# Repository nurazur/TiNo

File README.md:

# TiNo
[German Version](https://github.com/nurazur/TiNo/blob/master/LIESMICH.md)

"**TI**ny **NO**de": battery powered wireless sensor or wireless actor.
Target of the project is the development of small size , cost effective battery powered wireless sensors. The sensors communicate with gateways, like a raspberry pi.
The targets are:

- low cost (BOM under 5 Euro, as of 2020)
- very small size (matchbox)
- ultra low sleep current
- long battery life time: 5 years and more on a CR2032 cell
- long range (what ever this means :-), but its realy long)
- simple to build up
- communication security
- Plug&Play Firmware

Sensors can be almost any, like temperature, relative humidity, air pressure, altitude meter, light intensity, UV Index,
movement detectors, Reed switches, etc. However sensors have to be specified to work down to 2.2V. Otherwise the charge of the battery can not be fully used.

PCBs fit into low cost PVC boxes with the size of a matchbox that are readily available on the market.  

# Features
## General
- Voltage from ca. 1.8V to 3.6V
- Operates with a CR2032 cell up to 5 years
- various PCBs fitting into selected PVC boxes

## Sensors
- HTU21D
- SHT21, SHT20, SHT25
- SHT30, SHT31, SHT35
- BME280 (air pressure sensor)
- DS18B20 (ubiquitous temperature sensor)
- MAX31865 (PT100 temperature Sensor)
- AM312 (PIR movement sensor)
- I2C Bus based sensors can easily be integrated
- 4 digital GPIOs
- up to 4 analog GPIO's (dependent on hardware)

## Radio
- RFM69CW, RFM69HCW, RFM95 Module
- bidirectional communication
- ISM Band (Europe: 433MHz / 868MHz, US:315MHz / 915Mhz)
- 2GFSK Modulation
- Center frequency adjustable
- Frequency correction can be calibrated
- Transmit power from -18 dBm to 20dBm, 10 dBm typ.
- Link budget up to 120dB
- sensitivity -105 dBm typ.
- range t.b.d., but its looong!
- RF communication encrypted
- FEC (Forward Error Correction)
- Interleaver

## Baseband
- Atmel (Microchip) ATMega328p-au
- 32kByte Flash
- sleep current < 2µA mit external crystal 32.768kHz
- sleep current ca. 4µA with internal RC oscillator
- 1 MHz clock allows operating voltage down to 1.8V
- 8 MHz clock for gateway receiver
- I2C bus
- min 4 additional GPIO
- CPU can be locked to avoid reading the flash code

## System / Software
- Open Source Software C++
- Software can easily be adopted individually
- Programming tool is Arduino IDE
- Configuration of Nodes via serial interface (FTDI Adapter)
- configuration data and calibration data reside in EEPROM
- EEPROM encrypted
- Flashing
  - using ISP Adapter or
  - serial with FTDI Adapter and Bootloader
- up to 4 external interrupts (i.e. push buttons) can be configured

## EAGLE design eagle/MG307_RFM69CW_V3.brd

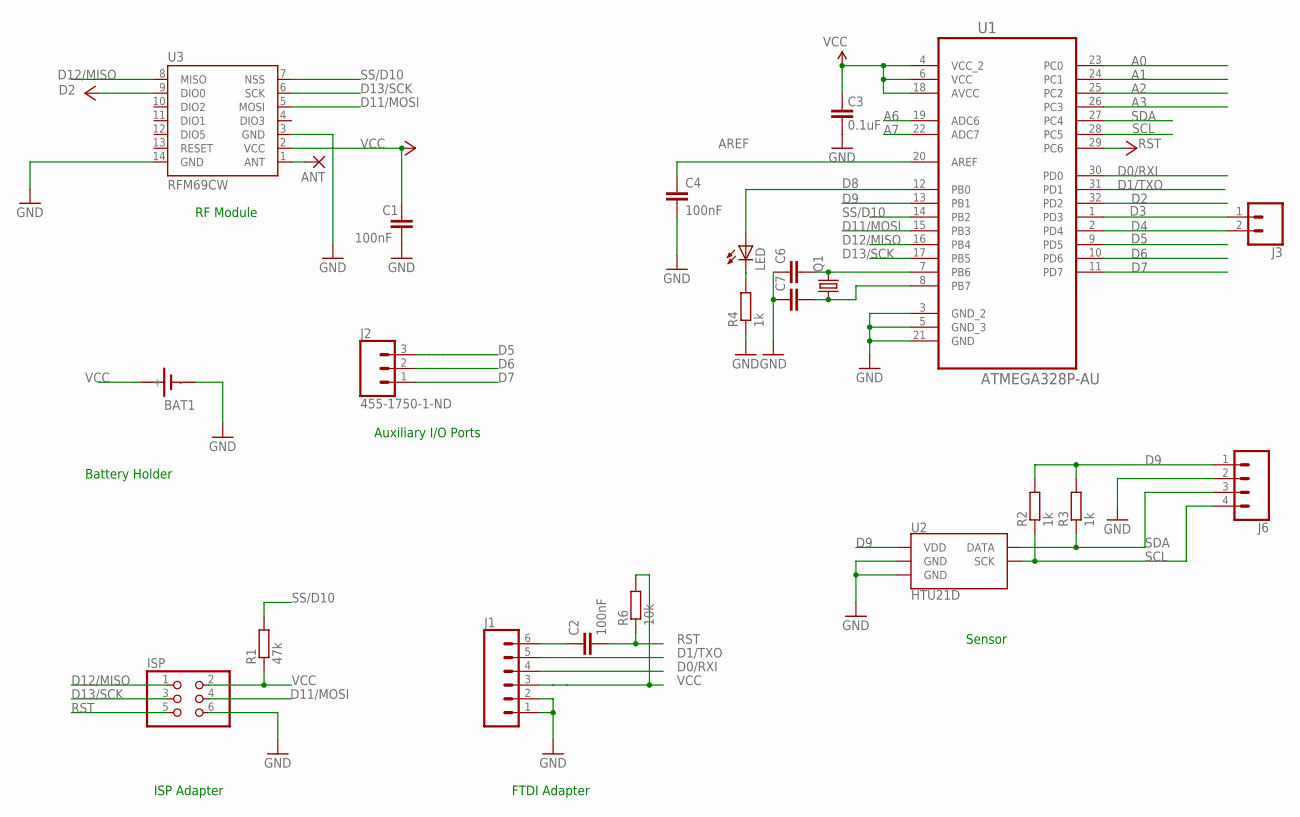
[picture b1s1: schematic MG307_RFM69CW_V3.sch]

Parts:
ANT: WIREPAD1,6/0,9; 1,6/0,9
BAT1: SN2032
C1, C2, C4: 100nF; C0603
C3: 0.1uF; 0603-CAP
C6, C7: C-EUC0402; C0402
ISP: PINHD-2X3; 2X03
J1: CONN_06SILK_FEMALE_PTH; 1X06
J2: 455-1750-1-ND; 1X03
J3: CONN_02; 1X02
J6: CONN_04; 1X04
LED: LEDCHIPLED_0603; CHIPLED_0603
Q1: CRYSTALTC26V; TC26V
R1: 47k; R0603
R2, R3, R4: 1k; R0603
R6: 10k; R0603
U1: ATMEGA328P-AU; QFP80P900X900X120-32N
U2: HTU21D; DFN-6-3X3-HTU21D
U3: RFM69CW

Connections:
A0: U1.23 (PC0)
A1: U1.24 (PC1)
A2: U1.25 (PC2)
A3: U1.26 (PC3)
A6: U1.19 (ADC6)
A7: U1.22 (ADC7)
ANT: ANT.1, U3.1 (ANT)
AREF: C4.1, U1.20 (AREF)
D0/RXI: J1.4, U1.30 (PD0)
D1/TXO: J1.5, U1.31 (PD1)
D2: U1.32 (PD2), U3.9 (DIO0)
D3: J3.1, U1.1 (PD3)
D4: J3.2, U1.2 (PD4)
D5: J2.3, U1.9 (PD5)
D6: J2.2, U1.10 (PD6)
D7: J2.1, U1.11 (PD7)
D8: LED.A, U1.12 (PB0)
D9: J6.1, R2.2, R3.2, U1.13 (PB1), U2.VDD
D11/MOSI: ISP.4, U1.15 (PB3), U3.5 (MOSI)
D12/MISO: ISP.1, U1.16 (PB4), U3.8 (MISO)
D13/SCK: ISP.3, U1.17 (PB5), U3.6 (SCK)
DTR: C2.1, J1.6
GND: BAT1.-, C1.2, C3.1, C4.2, C6.1, C7.1, ISP.6, J1.1, J1.2, J6.2, R4.1, U1.3 (GND_2), U1.5 (GND_3), U1.21 (GND), U2.7 (GND), U2.GND, U3.3 (GND), U3.14 (GND)
GND1: LED.C, R4.2
unnamed: C6.2, Q1.2, U1.7 (PB6)
unnamed: C7.2, Q1.1, U1.8 (PB7)
RESET: U3.13 (RESET)
RST: C2.2, ISP.5, R6.1, U1.29 (PC6)
SCL: J6.4, R2.1, U1.28 (PC5), U2.SCK
SDA: J6.3, R3.1, U1.27 (PC4), U2.DATA
SS/D10: R1.2, U1.14 (PB2), U3.7 (NSS)
VCC: BAT1.+, C1.1, C3.2, ISP.2, J1.3, R1.1, R6.2, U1.4 (VCC_2), U1.6 (VCC), U1.18 (AVCC), U3.2 (VCC)

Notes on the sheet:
RF Module
FTDI Adapter
ISP Adapter
Battery Holder
Auxiliary I/O Ports
Sensor

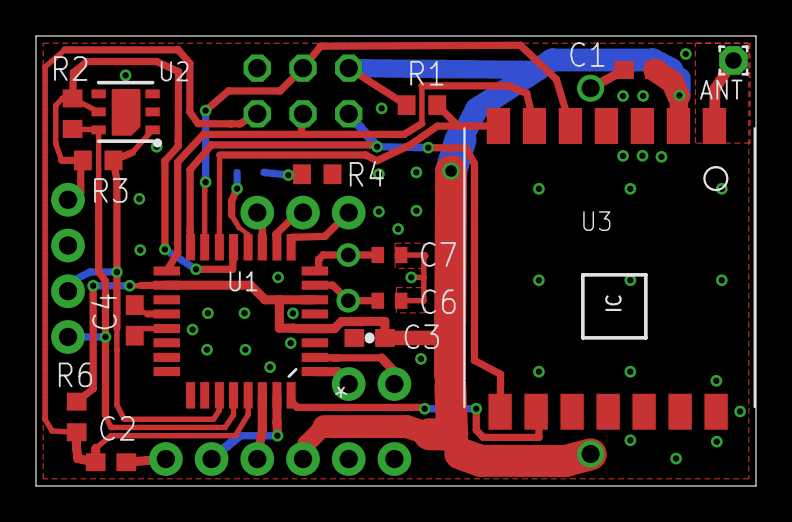
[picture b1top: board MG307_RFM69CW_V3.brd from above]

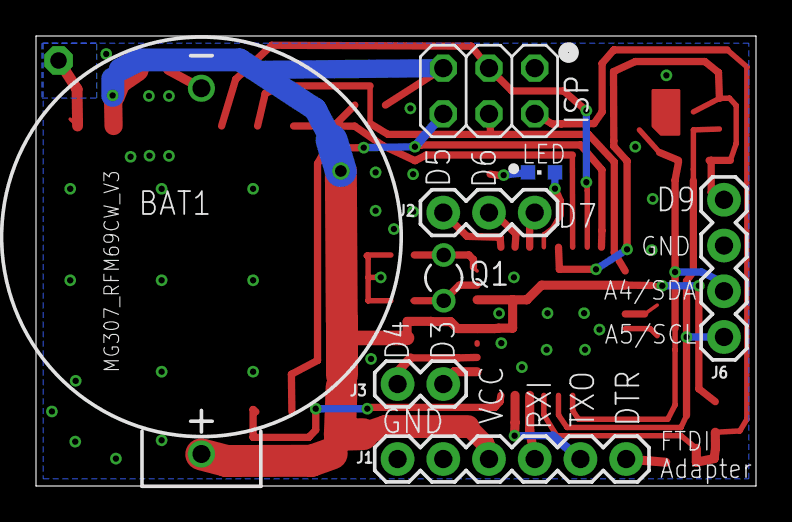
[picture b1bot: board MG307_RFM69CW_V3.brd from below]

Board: 2 copper layers, 40.0 x 25.0 mm, 23 parts (8 on the bottom side), 25 nets.

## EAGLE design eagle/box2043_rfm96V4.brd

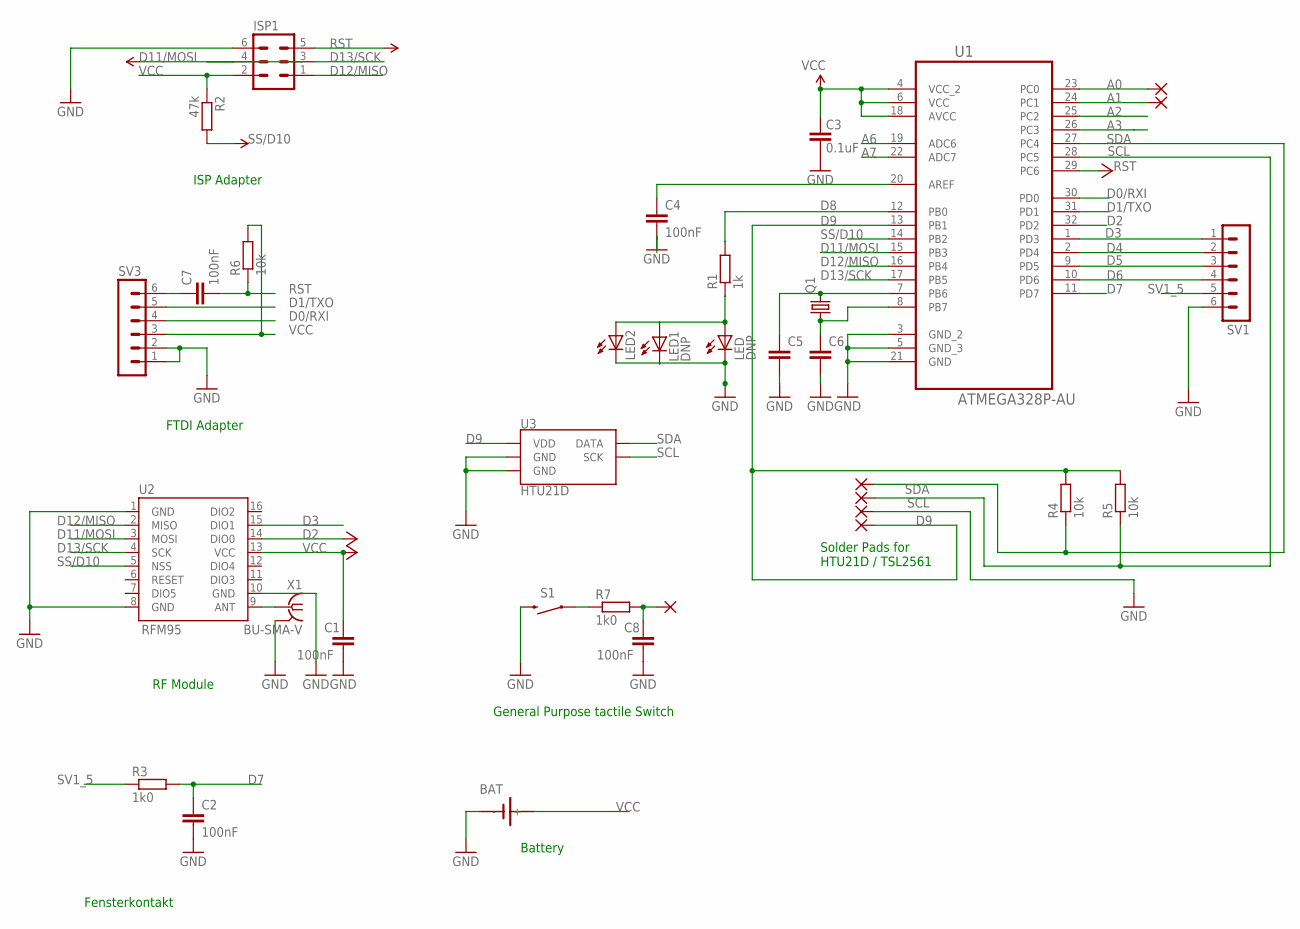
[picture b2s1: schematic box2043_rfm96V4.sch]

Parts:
A0, A1: SMD2; SMD1,27-2,54
BAT: SN2032
C1, C2, C4, C7, C8: 100nF; C0603
C3: 0.1uF; 0603-CAP
C5, C6: C-EUC0402; C0402
D9: SMD2; SMD1,27-2,54
GND: SMD2; SMD1,27-2,54
ISP1: MA03-2
LED: DNP; CHIPLED_0603
LED1: DNP; LED3MM
LED2: LEDCHIPLED_0603; CHIPLED_0603
N1: SMD2; SMD1,27-2,54
Q1: CRYSTALTC26V; TC26V
R1: 1k; R0603
R2: 47k; R0603
R3, R7: 1k0; R0603
R4, R5, R6: 10k; R0603
S1: MOMENTARY-SWITCH-SPST-PTH-RIGHT-ANGLE; TACTILE_SWITCH_PTH_RIGHT_ANGLE
SCL: SMD2; SMD1,27-2,54
SDA: SMD2; SMD1,27-2,54
SV1, SV3: MA06-1
U1: ATMEGA328P-AU; QFP80P900X900X120-32N
U2: RFM95; RFM95/96
U3: HTU21D; DFN-6-3X3-HTU21D
X1: BU-SMA-V

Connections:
A0: A0.1, U1.23 (PC0)
A1: A1.1, U1.24 (PC1)
A2: U1.25 (PC2)
A3: U1.26 (PC3)
A6: U1.19 (ADC6)
A7: U1.22 (ADC7)
D0/RXI: SV3.4, U1.30 (PD0)
D1/TXO: SV3.5, U1.31 (PD1)
D2: U1.32 (PD2), U2.14 (DIO0)
D3: SV1.1, U1.1 (PD3), U2.15 (DIO1)
D4: SV1.2, U1.2 (PD4)
D5: SV1.3, U1.9 (PD5)
D6: SV1.4, U1.10 (PD6)
D7: C2.1, R3.2, U1.11 (PD7)
D8: R1.2, U1.12 (PB0)
D9: D9.1, R4.2, R5.2, U1.13 (PB1), U3.VDD
D11/MOSI: ISP1.4, U1.15 (PB3), U2.3 (MOSI)
D12/MISO: ISP1.1, U1.16 (PB4), U2.2 (MISO)
D13/SCK: ISP1.3, U1.17 (PB5), U2.4 (SCK)
DTR: C7.1, SV3.6
GND: BAT.-, C1.2, C2.2, C3.1, C4.2, C5.2, C6.2, C8.2, GND.1, ISP1.6, LED.C, LED1.K (C), LED2.C, S1.2, SV1.6, SV3.1, SV3.2, U1.3 (GND_2), U1.5 (GND_3), U1.21 (GND), U2.1 (GND), U2.8 (GND), U2.10 (GND), U3.7 (GND), U3.GND, X1.2, X1.3 (2), X1.4 (2), X1.5 (2)
unnamed: U2.9 (ANT), X1.1
unnamed: C5.1, Q1.2, U1.7 (PB6)
unnamed: C4.1, U1.20 (AREF)
unnamed: R7.1, S1.1
unnamed: LED.A, LED1.A, LED2.A, R1.1
unnamed: C6.1, Q1.1, U1.8 (PB7)
unnamed: C8.1, N1.1, R7.2
RESET: U2.6 (RESET)
RST: C7.2, ISP1.5, R6.1, U1.29 (PC6)
SCL: R5.1, SCL.1, U1.28 (PC5), U3.SCK
SDA: R4.1, SDA.1, U1.27 (PC4), U3.DATA
SS/D10: R2.2, U1.14 (PB2), U2.5 (NSS)
SV1_5: R3.1, SV1.5
VCC: BAT.+, C1.1, C3.2, ISP1.2, R2.1, R6.2, SV3.3, U1.4 (VCC_2), U1.6 (VCC), U1.18 (AVCC), U2.13 (VCC)

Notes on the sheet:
ISP Adapter
Solder Pads for HTU21D / TSL2561
Fensterkontakt
Battery
RF Module
FTDI Adapter
General Purpose tactile Switch

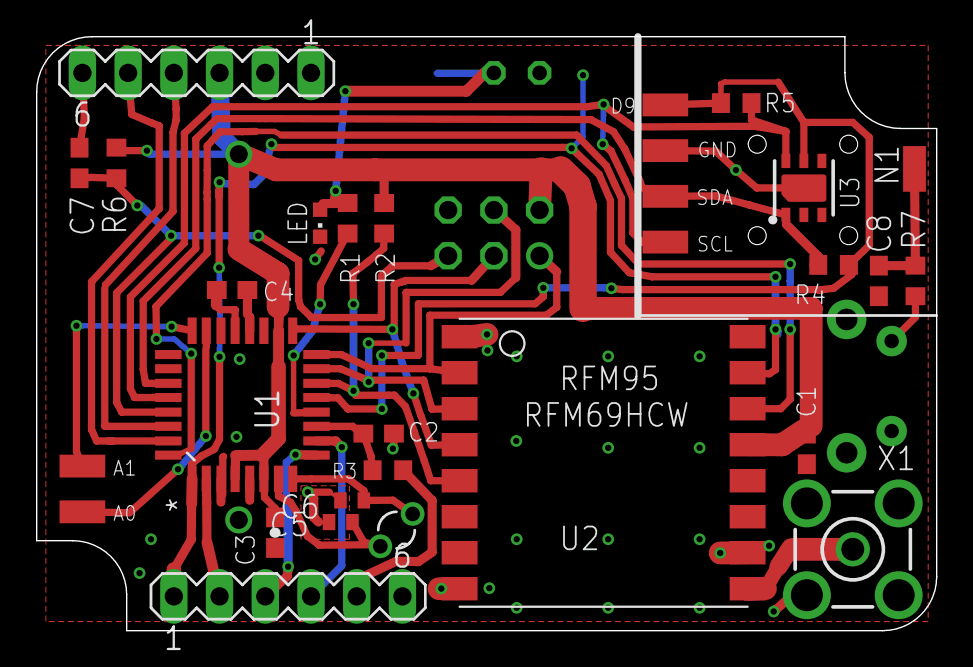
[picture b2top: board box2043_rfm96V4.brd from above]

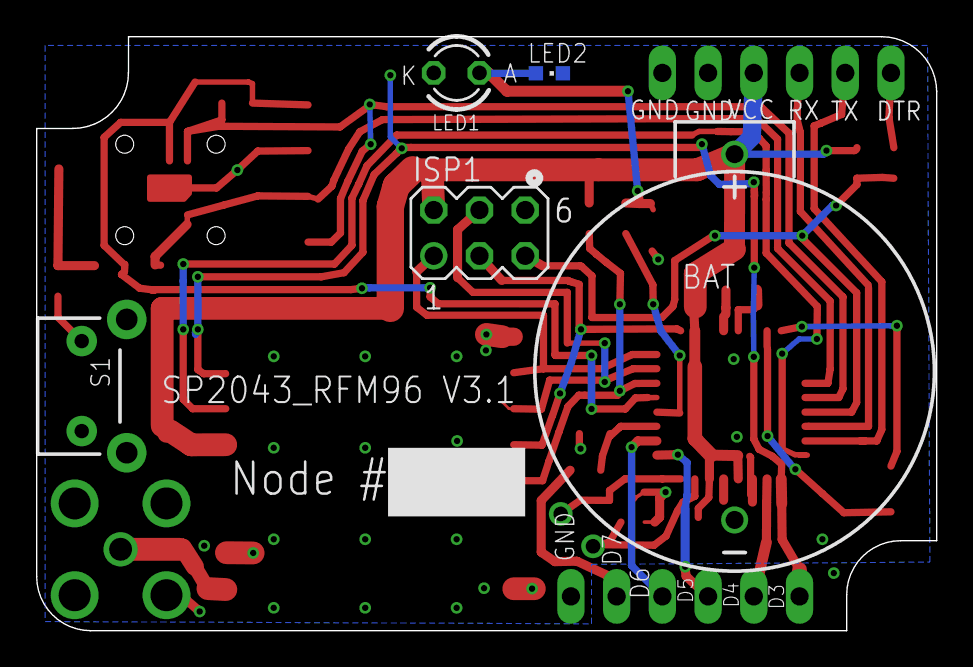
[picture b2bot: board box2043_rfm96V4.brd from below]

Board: 2 copper layers, 50.0 x 33.0 mm, 35 parts (5 on the bottom side), 30 nets.

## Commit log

2018-11-26 initial commit - added project files
2018-11-26 added libraries Mac, calibration, configuration, RFM69
2018-11-26 remove spaces in file
2018-11-26 corrections of typos
2018-11-26 correct an issue with the character set used.
2018-11-26 issues with character set
2018-11-27 fix batch files to launch eepromer
2018-11-27 fix eepromer
2018-11-27 add pic
2018-11-27 change readme.md
2018-11-27 ~fix readme.md
2018-11-27 change directory structure
2018-11-27 update dokumentation
2018-11-27 update doc
2018-11-28 add picture
2018-11-28 change readme
2018-11-28 change picture size
2018-11-29 add JSON file for Arduino IDE
2018-11-29 add package_tino_index.json change eepromer tool
2018-11-29 fixes
2018-11-29 formatting fixes
2018-11-30 update doku
2018-11-30 update doku, testing anchors
2018-11-30 update dokumentation with Informnation about the EEPROMer Tool
2018-11-30 update dokumentation, test tables
2018-11-30 fix docu
2018-11-30 test tables in docu
2018-11-30 first coomit of HTU21D and SHT3x linraries in the SoftwareWire flavor
2018-12-01 add eepromer tool for Raspbian. add example batch files. Added some command line options.
2018-12-01 change picture in readme.md
2018-12-01 Test table
2018-12-01 test table in dokumentation
2018-12-01 change picture
2018-12-02 work on docu
2018-12-04 update documentation
2018-12-04 re-organize tools section
2018-12-04 new release
2018-12-05 uppercase hash
2018-12-30 update german documentation
2019-01-02 add eagle PCB designs
2019-01-05 Link to PCB design directory added
2019-07-08 Add BOM for PVB's
2019-09-02 Add support for Python 3
2019-09-04 add TiNo Logo
2019-09-04 RF drivers have now a generic abstract base class. This allows in future to add new hardware easily, independent from higher software levels. "mac" is renamed to "data link layer" whis is better unde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
2019-09-04 new calibration tools for version 2.0, ready for python 3
2019-09-04 example sketches for sensor and gateway, version 2.0
2019-09-04 add library for BME280 with SoftwareWire I2C bus driver support
2019-09-05 Test Arduino IDE for version 2.0.0
2019-09-05 Test Arduino IDE with version 2.0.1 (published)
2019-09-06 provide correct configuaration tool for Raspberry Pi
2020-01-21 cp command: don't save parameters that are automatically written into EEPROM by firmware
2020-01-21 update LIESMICH to clarify usage of master branch
2020-01-21 add TiNo Data protocol specification Version 2.0.1
2020-01-21 some corrections
2020-01-21 added hint to ioBroker, added link to documentation (german)
2020-02-20 Update German Documentation, add english documentation
2020-02-21 test
2020-02-21 re-test
2020-02-22 make konfiguration tool 100% compatible with Python 3
2020-02-24 Add Protocol documents
2020-02-24 update: BME280 Sensor is supported
2020-02-24 Update Version 2.1.0 - rolling codes, gateway mode, BME280 support
2020-02-25 Add support for TI Chip CC1101
2020-02-25 Update to Version 2.1.0, BME280 support, CC1101 support
2020-02-27 correct an error in v2.1 release
2020-04-24 HTU21D Sensor for HomeMatic
2020-05-21 Typo korrigiert
2021-02-03 add pinout pics to documentation
2021-02-03 correct error in picture
2021-02-04 update english Documentation
2021-02-04 some corrections of typos in english documentation
2021-05-29 new sensors: MAX31865 and AM312
2021-05-30 release 2.2.0
2021-05-31 correct typo (wrong braces)
2021-07-03 Bug fix: correct serial outputs.
2021-08-26 Correction of version and date in welcome string
2021-10-11 correct bug in RFM69::setDataShaping
2022-03-04 initial release 3.0.1
2022-03-04 update package index for arduino IDE
2022-03-04 update receive.ino (bug fix)
2022-03-04 revert package index to 3.0.1
2022-03-04 again increase package index to 3.0.2
2022-03-04 clean up release 3.0.2
2022-03-04 update documentation to Version 3
2022-09-02 configuration tool: some minor bug fixes some minor improvements add possibility to define a bit in bitfields in configuration files. example: sensorconfig.brightness=1
2024-11-30 add PCB Version 3.5 Gerber and schematics

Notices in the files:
parts and their libraries:
SparkFun-Connectors: Licensing: Creative Commons ShareAlike 4.0 International - https://creativecommons.org/licenses/by-sa/4.0
SparkFun-Sensors: Licensing: CC v3.0 Share-Alike You are welcome to use this library for commercial purposes.
